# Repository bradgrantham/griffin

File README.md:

# m68k-leftovers

An M68000 homebrew SBC.  See the [design notes](griffin.yml).

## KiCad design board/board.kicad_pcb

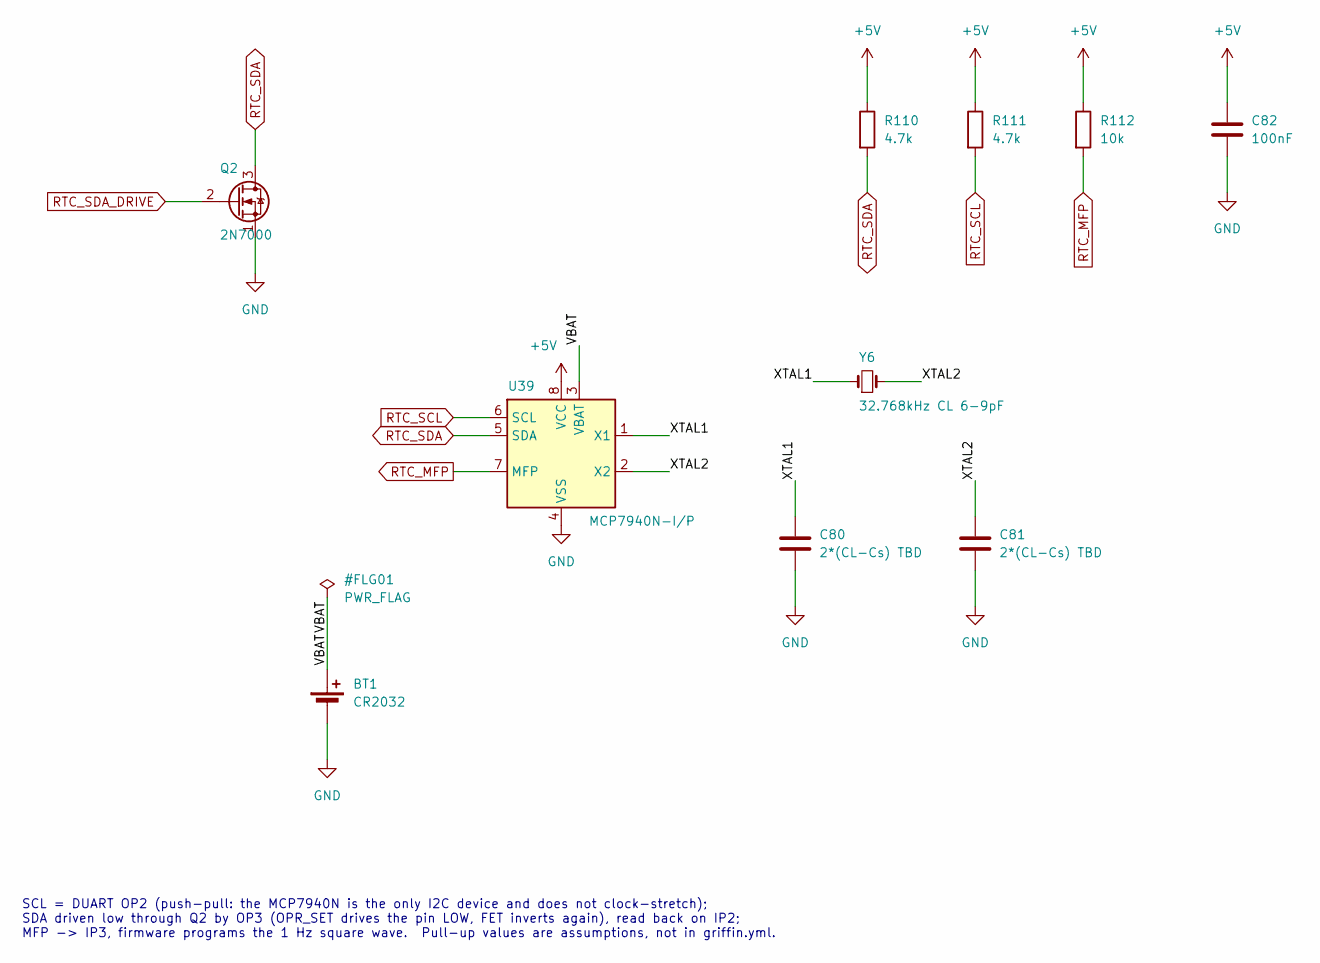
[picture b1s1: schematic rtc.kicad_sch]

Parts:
BT1: CR2032; BatteryHolder_Keystone_3034_1x20mm
C80, C81: 2*(CL-Cs) TBD; C_Disc_D5.0mm_W2.5mm_P5.00mm
C82: 100nF; C_Disc_D5.0mm_W2.5mm_P5.00mm
Q2: 2N7000; TO-92_Inline
R110, R111: 4.7k; R_Axial_DIN0207_L6.3mm_D2.5mm_P10.16mm_Horizontal
R112: 10k; R_Axial_DIN0207_L6.3mm_D2.5mm_P10.16mm_Horizontal
U39: MCP7940N-I/P; DIP-8_W7.62mm
Y6: 32.768kHz CL 6-9pF; Crystal_C26-LF_D2.1mm_L6.5mm_Vertical

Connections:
+5V: C82.1, R110.1, R111.1, R112.1, U39.8 (VCC); also elsewhere on the board
/RTC/XTAL1: C80.1, U39.1 (X1), Y6.1
/RTC/XTAL2: C81.1, U39.2 (X2), Y6.2
GND: BT1.2 (-), C80.2, C81.2, C82.2, Q2.1 (S), U39.4 (VSS); also elsewhere on the board
RTC_MFP: R112.2, U39.7 (MFP)
RTC_SCL: R111.2, U39.6 (SCL)
RTC_SDA: Q2.3 (D), R110.2, U39.5 (SDA)
RTC_SDA_DRIVE: Q2.2 (G)

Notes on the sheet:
SCL = DUART OP2 (push-pull: the MCP7940N is the only I2C device and does not clock-stretch); SDA driven low through Q2 by OP3 (OPR_SET drives the pin LOW, FET inverts again), read back on IP2; MFP -> IP3, firmware programs the 1 Hz square wave. Pull-up values are assumptions, not in griffin.yml.

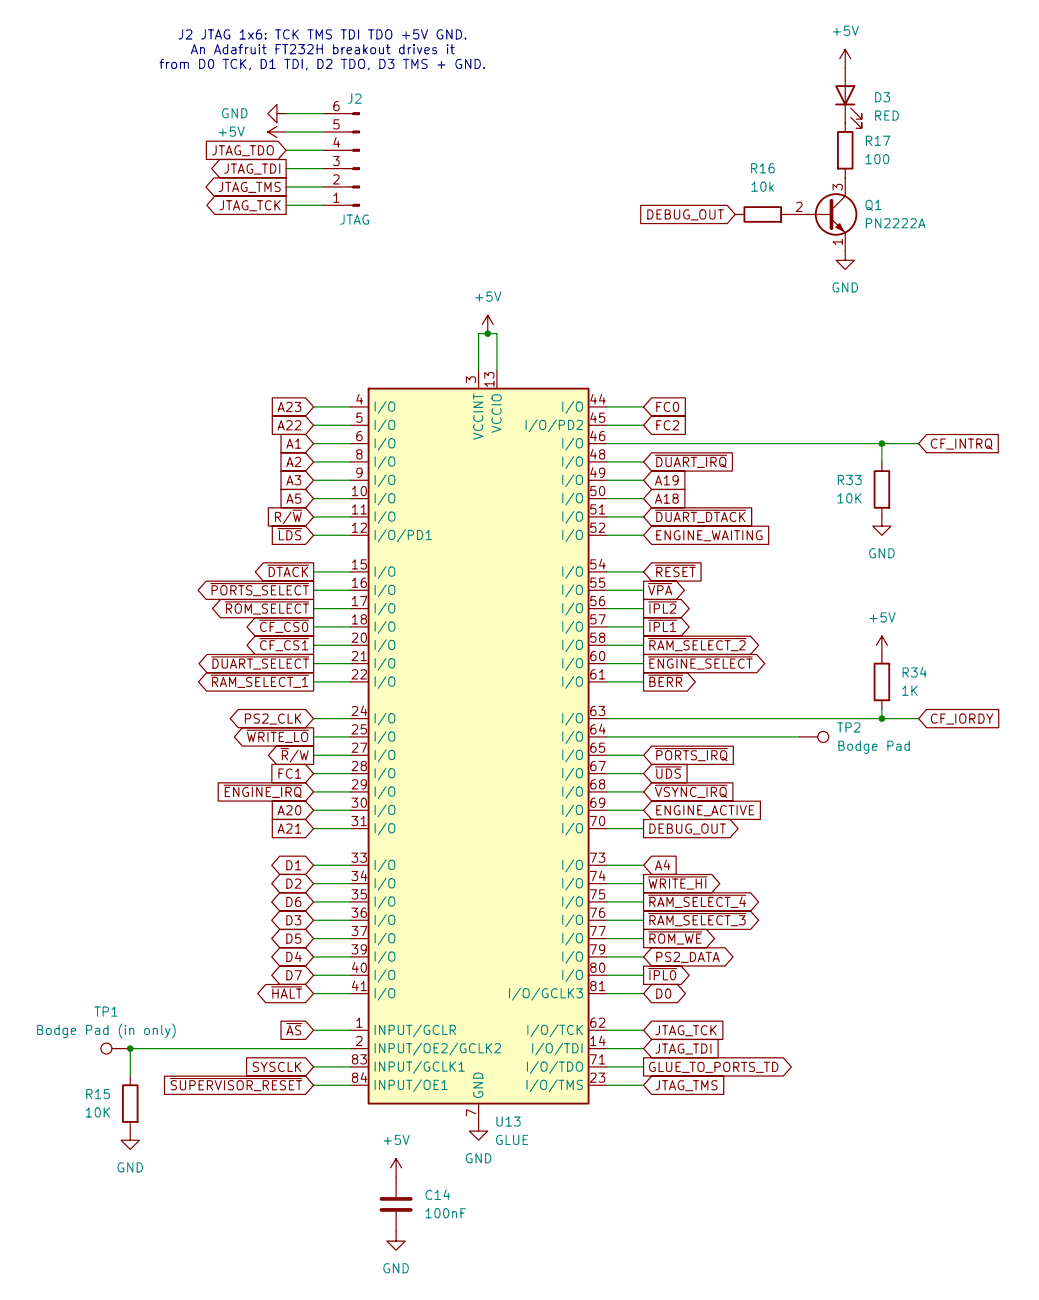
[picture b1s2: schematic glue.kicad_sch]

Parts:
C14: 100nF; C_Disc_D5.0mm_W2.5mm_P5.00mm
D3: RED; LED_D3.0mm
J2: JTAG; PinHeader_1x06_P2.54mm_Vertical
Q1: PN2222A; TO-92_Inline
R15, R33: 10K; R_Axial_DIN0207_L6.3mm_D2.5mm_P10.16mm_Horizontal
R16: 10k; R_Axial_DIN0207_L6.3mm_D2.5mm_P10.16mm_Horizontal
R17: 100; R_Axial_DIN0207_L6.3mm_D2.5mm_P10.16mm_Horizontal
R34: 1K; R_Axial_DIN0207_L6.3mm_D2.5mm_P10.16mm_Horizontal
TP1: Bodge Pad (in only)
TP2: Bodge Pad
U13: GLUE; PLCC-84_THT-Socket

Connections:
+5V: C14.1, D3.2 (A), J2.5, R34.1, U13.3 (VCCINT), U13.13 (VCCIO), U13.26 (VCCIO), U13.38 (VCCIO), U13.43 (VCCINT), U13.53 (VCCIO), U13.66 (VCCIO), U13.78 (VCCIO); also elsewhere on the board
A1: U13.6 (I/O); also elsewhere on the board
A2: U13.8 (I/O); also elsewhere on the board
A3: U13.9 (I/O); also elsewhere on the board
A4: U13.73 (I/O); also elsewhere on the board
A5: U13.10 (I/O); also elsewhere on the board
A18: U13.50 (I/O); also elsewhere on the board
A19: U13.49 (I/O); also elsewhere on the board
A20: U13.30 (I/O); also elsewhere on the board
A21: U13.31 (I/O); also elsewhere on the board
A22: U13.5 (I/O); also elsewhere on the board
A23: U13.4 (I/O); also elsewhere on the board
CF_INTRQ: R33.1, U13.46 (I/O); also elsewhere on the board
CF_IORDY: R34.2, U13.63 (I/O); also elsewhere on the board
D0: U13.81 (I/O/GCLK3); also elsewhere on the board
D1: U13.33 (I/O); also elsewhere on the board
D2: U13.34 (I/O); also elsewhere on the board
D3: U13.36 (I/O); also elsewhere on the board
D4: U13.39 (I/O); also elsewhere on the board
D5: U13.37 (I/O); also elsewhere on the board
D6: U13.35 (I/O); also elsewhere on the board
D7: U13.40 (I/O); also elsewhere on the board
DEBUG_OUT: R16.1, U13.70 (I/O)
ENGINE_ACTIVE: U13.69 (I/O); also elsewhere on the board
ENGINE_WAITING: U13.52 (I/O); also elsewhere on the board
FC0: U13.44 (I/O); also elsewhere on the board
FC1: U13.28 (I/O); also elsewhere on the board
FC2: U13.45 (I/O/PD2); also elsewhere on the board
GLUE_TO_PORTS_TD: U13.71 (I/O/TDO); also elsewhere on the board
GND: C14.2, J2.6, Q1.1 (E), R15.2, R33.2, U13.7 (GND), U13.19 (GND), U13.32 (GND), U13.42 (GND), U13.47 (GND), U13.59 (GND), U13.72 (GND), U13.82 (GND); also elsewhere on the board
JTAG_TCK: J2.1, U13.62 (I/O/TCK); also elsewhere on the board
JTAG_TDI: J2.3, U13.14 (I/O/TDI)
JTAG_TDO: J2.4; also elsewhere on the board
JTAG_TMS: J2.2, U13.23 (I/O/TMS); also elsewhere on the board
unnamed: D3.1 (K), R17.1
unnamed: Q1.2 (B), R16.2
unnamed: Q1.3 (C), R17.2
unnamed: TP2.1, U13.64 (I/O)
unnamed: R15.1, TP1.1, U13.2 (INPUT/OE2/GCLK2)
PS2_CLK: U13.24 (I/O); also elsewhere on the board
PS2_DATA: U13.79 (I/O); also elsewhere on the board
R/~W: U13.11 (I/O); also elsewhere on the board
SYSCLK: U13.83 (INPUT/GCLK1); also elsewhere on the board
~AS: U13.1 (INPUT/GCLR); also elsewhere on the board
~BERR: U13.61 (I/O); also elsewhere on the board
~CF_CS0: U13.18 (I/O); also elsewhere on the board
~CF_CS1: U13.20 (I/O); also elsewhere on the board
~DTACK: U13.15 (I/O); also elsewhere on the board
~DUART_DTACK: U13.51 (I/O)
~DUART_IRQ: U13.48 (I/O)
~DUART_SELECT: U13.21 (I/O)
~ENGINE_IRQ: U13.29 (I/O); also elsewhere on the board
~ENGINE_SELECT: U13.60 (I/O); also elsewhere on the board
~HALT: U13.41 (I/O); also elsewhere on the board
~IPL0: U13.80 (I/O); also elsewhere on the board
~IPL1: U13.57 (I/O); also elsewhere on the board
~IPL2: U13.56 (I/O); also elsewhere on the board
~LDS: U13.12 (I/O/PD1); also elsewhere on the board
~PORTS_IRQ: U13.65 (I/O); also elsewhere on the board
~PORTS_SELECT: U13.16 (I/O); also elsewhere on the board
~RAM_SELECT_1: U13.22 (I/O); also elsewhere on the board
~RAM_SELECT_2: U13.58 (I/O); also elsewhere on the board
~RAM_SELECT_3: U13.76 (I/O); also elsewhere on the board
~RAM_SELECT_4: U13.75 (I/O); also elsewhere on the board
~RESET: U13.54 (I/O); also elsewhere on the board
~ROM_SELECT: U13.17 (I/O); also elsewhere on the board
~ROM_WE: U13.77 (I/O); also elsewhere on the board
~R/W: U13.27 (I/O); also elsewhere on the board
~SUPERVISOR_RESET: U13.84 (INPUT/OE1); also elsewhere on the board
~UDS: U13.67 (I/O); also elsewhere on the board
~VPA: U13.55 (I/O); also elsewhere on the board
~VSYNC_IRQ: U13.68 (I/O); also elsewhere on the board
~WRITE_HI: U13.74 (I/O); also elsewhere on the board
~WRITE_LO: U13.25 (I/O); also elsewhere on the board

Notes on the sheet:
J2 JTAG 1x6: TCK TMS TDI TDO +5V GND. An Adafruit FT232H breakout drives it from D0 TCK, D1 TDI, D2 TDO, D3 TMS + GND.

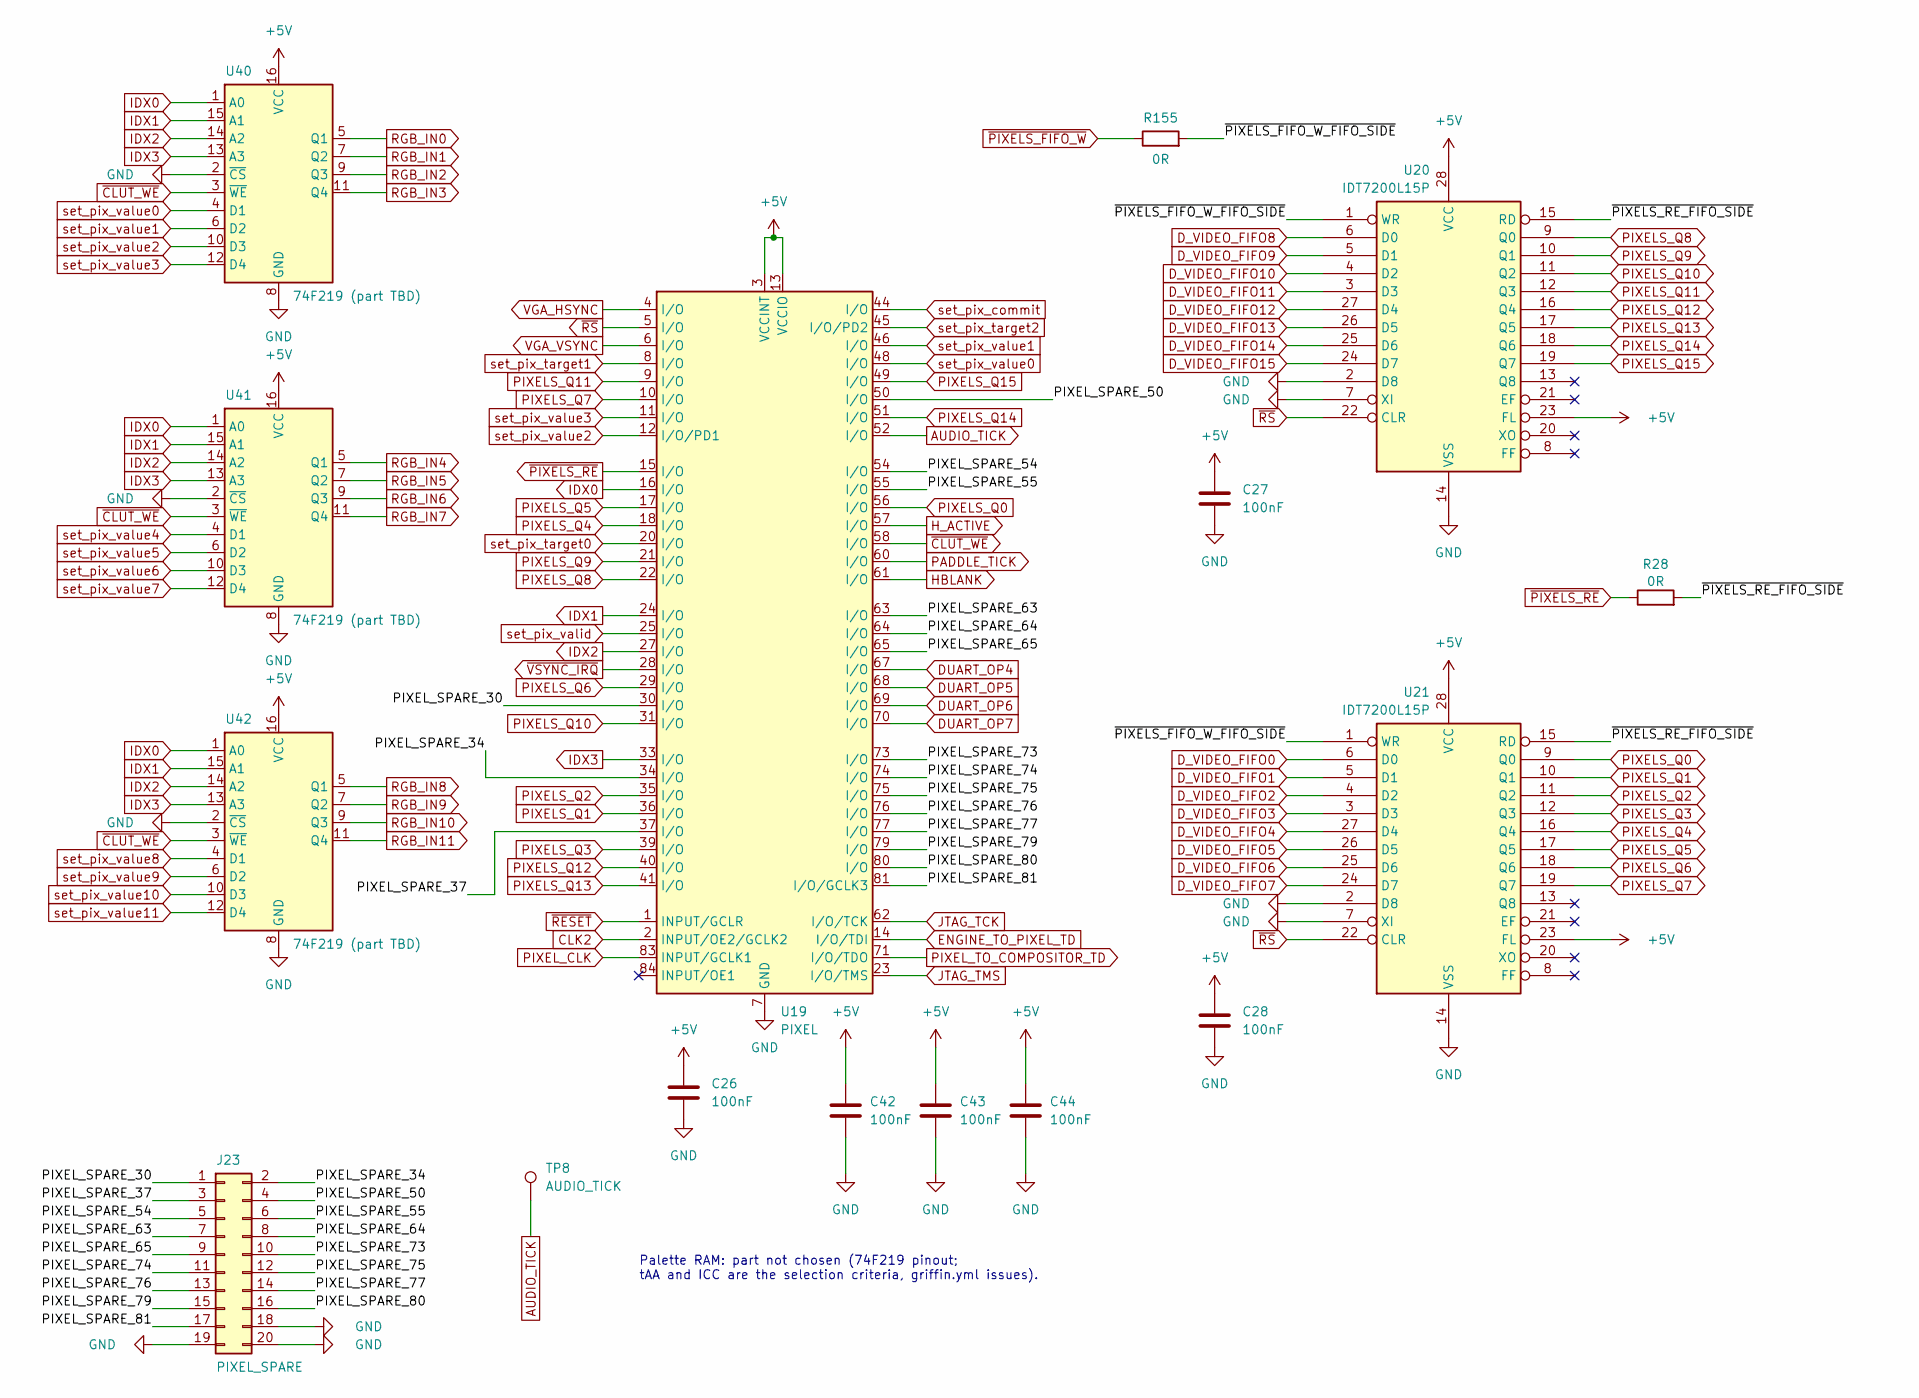
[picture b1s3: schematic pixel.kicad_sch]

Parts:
C26, C27, C28, C42, C43, C44: 100nF; C_Disc_D5.0mm_W2.5mm_P5.00mm
J23: PIXEL_SPARE; PinHeader_2x10_P2.54mm_Vertical
R28, R155: 0R; R_Axial_DIN0207_L6.3mm_D2.5mm_P10.16mm_Horizontal
TP8: AUDIO_TICK; TestPoint_Pad_D1.5mm
U19: PIXEL; PLCC-84_THT-Socket
U20, U21: IDT7200L15P; DIP-28_W7.62mm
U40, U41, U42: 74F219 (part TBD); DIP-16_W7.62mm

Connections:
+5V: C26.1, C27.1, C28.1, C42.1, C43.1, C44.1, U19.3 (VCCINT), U19.13 (VCCIO), U19.26 (VCCIO), U19.38 (VCCIO), U19.43 (VCCINT), U19.53 (VCCIO), U19.66 (VCCIO), U19.78 (VCCIO), U20.23 (FL), U20.28 (VCC), U21.23 (FL), U21.28 (VCC), U40.16 (VCC), U41.16 (VCC), U42.16 (VCC); also elsewhere on the board
/PIXEL/PIXEL_SPARE_30: J23.1, U19.30 (I/O)
/PIXEL/PIXEL_SPARE_34: J23.2, U19.34 (I/O)
/PIXEL/PIXEL_SPARE_37: J23.3, U19.37 (I/O)
/PIXEL/PIXEL_SPARE_50: J23.4, U19.50 (I/O)
/PIXEL/PIXEL_SPARE_54: J23.5, U19.54 (I/O)
/PIXEL/PIXEL_SPARE_55: J23.6, U19.55 (I/O)
/PIXEL/PIXEL_SPARE_63: J23.7, U19.63 (I/O)
/PIXEL/PIXEL_SPARE_64: J23.8, U19.64 (I/O)
/PIXEL/PIXEL_SPARE_65: J23.9, U19.65 (I/O)
/PIXEL/PIXEL_SPARE_73: J23.10, U19.73 (I/O)
/PIXEL/PIXEL_SPARE_74: J23.11, U19.74 (I/O)
/PIXEL/PIXEL_SPARE_75: J23.12, U19.75 (I/O)
/PIXEL/PIXEL_SPARE_76: J23.13, U19.76 (I/O)
/PIXEL/PIXEL_SPARE_77: J23.14, U19.77 (I/O)
/PIXEL/PIXEL_SPARE_79: J23.15, U19.79 (I/O)
/PIXEL/PIXEL_SPARE_80: J23.16, U19.80 (I/O)
/PIXEL/PIXEL_SPARE_81: J23.17, U19.81 (I/O/GCLK3)
/PIXEL/~PIXELS_FIFO_W_FIFO_SIDE: R155.2, U20.1 (WR), U21.1 (WR)
/PIXEL/~PIXELS_RE_FIFO_SIDE: R28.2, U20.15 (RD), U21.15 (RD)
AUDIO_TICK: TP8.1, U19.52 (I/O)
CLK2: U19.2 (INPUT/OE2/GCLK2); also elsewhere on the board
DUART_OP4: U19.67 (I/O)
DUART_OP5: U19.68 (I/O)
DUART_OP6: U19.69 (I/O)
DUART_OP7: U19.70 (I/O)
D_VIDEO_FIFO0: U21.6 (D0); also elsewhere on the board
D_VIDEO_FIFO1: U21.5 (D1); also elsewhere on the board
D_VIDEO_FIFO2: U21.4 (D2); also elsewhere on the board
D_VIDEO_FIFO3: U21.3 (D3); also elsewhere on the board
D_VIDEO_FIFO4: U21.27 (D4); also elsewhere on the board
D_VIDEO_FIFO5: U21.26 (D5); also elsewhere on the board
D_VIDEO_FIFO6: U21.25 (D6); also elsewhere on the board
D_VIDEO_FIFO7: U21.24 (D7); also elsewhere on the board
D_VIDEO_FIFO8: U20.6 (D0); also elsewhere on the board
D_VIDEO_FIFO9: U20.5 (D1); also elsewhere on the board
D_VIDEO_FIFO10: U20.4 (D2); also elsewhere on the board
D_VIDEO_FIFO11: U20.3 (D3); also elsewhere on the board
D_VIDEO_FIFO12: U20.27 (D4); also elsewhere on the board
D_VIDEO_FIFO13: U20.26 (D5); also elsewhere on the board
D_VIDEO_FIFO14: U20.25 (D6); also elsewhere on the board
D_VIDEO_FIFO15: U20.24 (D7); also elsewhere on the board
ENGINE_TO_PIXEL_TD: U19.14 (I/O/TDI); also elsewhere on the board
GND: C26.2, C27.2, C28.2, C42.2, C43.2, C44.2, J23.18, J23.19, J23.20, U19.7 (GND), U19.19 (GND), U19.32 (GND), U19.42 (GND), U19.47 (GND), U19.59 (GND), U19.72 (GND), U19.82 (GND), U20.2 (D8), U20.7 (XI), U20.14 (VSS), U21.2 (D8), U21.7 (XI), U21.14 (VSS), U40.2 (~CS), U40.8 (GND), U41.2 (~CS), U41.8 (GND), U42.2 (~CS), U42.8 (GND); also elsewhere on the board
HBLANK: U19.61 (I/O); also elsewhere on the board
H_ACTIVE: U19.57 (I/O); also elsewhere on the board
IDX0: U19.16 (I/O), U40.1 (A0), U41.1 (A0), U42.1 (A0)
IDX1: U19.24 (I/O), U40.15 (A1), U41.15 (A1), U42.15 (A1)
IDX2: U19.27 (I/O), U40.14 (A2), U41.14 (A2), U42.14 (A2)
IDX3: U19.33 (I/O), U40.13 (A3), U41.13 (A3), U42.13 (A3)
JTAG_TCK: U19.62 (I/O/TCK); also elsewhere on the board
JTAG_TMS: U19.23 (I/O/TMS); also elsewhere on the board
PADDLE_TICK: U19.60 (I/O); also elsewhere on the board
PIXELS_Q0: U19.56 (I/O), U21.9 (Q0)
PIXELS_Q1: U19.36 (I/O), U21.10 (Q1)
PIXELS_Q2: U19.35 (I/O), U21.11 (Q2)
PIXELS_Q3: U19.39 (I/O), U21.12 (Q3)
PIXELS_Q4: U19.18 (I/O), U21.16 (Q4)
PIXELS_Q5: U19.17 (I/O), U21.17 (Q5)
PIXELS_Q6: U19.29 (I/O), U21.18 (Q6)
PIXELS_Q7: U19.10 (I/O), U21.19 (Q7)
PIXELS_Q8: U19.22 (I/O), U20.9 (Q0)
PIXELS_Q9: U19.21 (I/O), U20.10 (Q1)
PIXELS_Q10: U19.31 (I/O), U20.11 (Q2)
PIXELS_Q11: U19.9 (I/O), U20.12 (Q3)
PIXELS_Q12: U19.40 (I/O), U20.16 (Q4)
PIXELS_Q13: U19.41 (I/O), U20.17 (Q5)
PIXELS_Q14: U19.51 (I/O), U20.18 (Q6)
PIXELS_Q15: U19.49 (I/O), U20.19 (Q7)
PIXEL_CLK: U19.83 (INPUT/GCLK1); also elsewhere on the board
PIXEL_TO_COMPOSITOR_TD: U19.71 (I/O/TDO); also elsewhere on the board
RGB_IN0: U40.5 (Q1); also elsewhere on the board
RGB_IN1: U40.7 (Q2); also elsewhere on the board
RGB_IN2: U40.9 (Q3); also elsewhere on the board
RGB_IN3: U40.11 (Q4); also elsewhere on the board
RGB_IN4: U41.5 (Q1); also elsewhere on the board
RGB_IN5: U41.7 (Q2); also elsewhere on the board
RGB_IN6: U41.9 (Q3); also elsewhere on the board
RGB_IN7: U41.11 (Q4); also elsewhere on the board
RGB_IN8: U42.5 (Q1); also elsewhere on the board
RGB_IN9: U42.7 (Q2); also elsewhere on the board
RGB_IN10: U42.9 (Q3); also elsewhere on the board
RGB_IN11: U42.11 (Q4); also elsewhere on the board
VGA_HSYNC: U19.4 (I/O); also elsewhere on the board
VGA_VSYNC: U19.6 (I/O); also elsewhere on the board
set_pix_commit: U19.44 (I/O); also elsewhere on the board
set_pix_target0: U19.20 (I/O); also elsewhere on the board
set_pix_target1: U19.8 (I/O); also elsewhere on the board
set_pix_target2: U19.45 (I/O/PD2); also elsewhere on the board
set_pix_valid: U19.25 (I/O); also elsewhere on the board
set_pix_value0: U19.48 (I/O), U40.4 (D1); also elsewhere on the board
set_pix_value1: U19.46 (I/O), U40.6 (D2); also elsewhere on the board
set_pix_value2: U19.12 (I/O/PD1), U40.10 (D3); also elsewhere on the board
set_pix_value3: U19.11 (I/O), U40.12 (D4); also elsewhere on the board
set_pix_value4: U41.4 (D1); also elsewhere on the board
set_pix_value5: U41.6 (D2); also elsewhere on the board
set_pix_value6: U41.10 (D3); also elsewhere on the board
set_pix_value7: U41.12 (D4); also elsewhere on the board
set_pix_value8: U42.4 (D1); also elsewhere on the board
set_pix_value9: U42.6 (D2); also elsewhere on the board
set_pix_value10: U42.10 (D3); also elsewhere on the board
set_pix_value11: U42.12 (D4); also elsewhere on the board
~CLUT_WE: U19.58 (I/O), U40.3 (~WE), U41.3 (~WE), U42.3 (~WE)
~PIXELS_FIFO_W: R155.1; also elsewhere on the board
~PIXELS_RE: R28.1, U19.15 (I/O)
~RESET: U19.1 (INPUT/GCLR); also elsewhere on the board
~RS: U19.5 (I/O), U20.22 (CLR), U21.22 (CLR); also elsewhere on the board
~VSYNC_IRQ: U19.28 (I/O); also elsewhere on the board

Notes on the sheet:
Palette RAM: part not chosen (74F219 pinout; tAA and ICC are the selection criteria, griffin.yml issues).

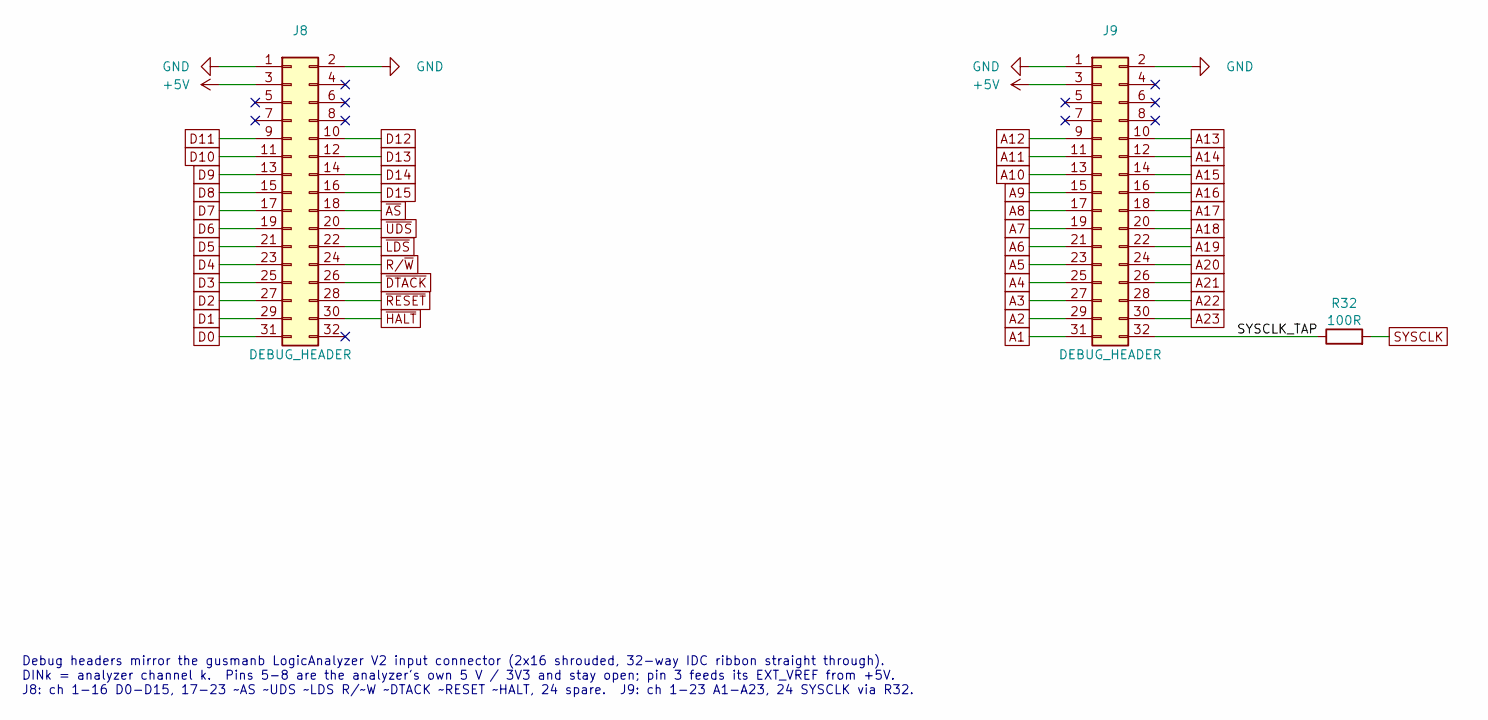
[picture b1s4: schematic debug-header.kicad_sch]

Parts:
J8, J9: DEBUG_HEADER; IDC-Header_2x16_P2.54mm_Vertical
R32: 100R; R_Axial_DIN0207_L6.3mm_D2.5mm_P10.16mm_Horizontal

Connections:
+5V: J8.3, J9.3; also elsewhere on the board
/DEBUG_HEADER/SYSCLK_TAP: J9.32, R32.1
A1: J9.31; also elsewhere on the board
A2: J9.29; also elsewhere on the board
A3: J9.27; also elsewhere on the board
A4: J9.25; also elsewhere on the board
A5: J9.23; also elsewhere on the board
A6: J9.21; also elsewhere on the board
A7: J9.19; also elsewhere on the board
A8: J9.17; also elsewhere on the board
A9: J9.15; also elsewhere on the board
A10: J9.13; also elsewhere on the board
A11: J9.11; also elsewhere on the board
A12: J9.9; also elsewhere on the board
A13: J9.10; also elsewhere on the board
A14: J9.12; also elsewhere on the board
A15: J9.14; also elsewhere on the board
A16: J9.16; also elsewhere on the board
A17: J9.18; also elsewhere on the board
A18: J9.20; also elsewhere on the board
A19: J9.22; also elsewhere on the board
A20: J9.24; also elsewhere on the board
A21: J9.26; also elsewhere on the board
A22: J9.28; also elsewhere on the board
A23: J9.30; also elsewhere on the board
D0: J8.31; also elsewhere on the board
D1: J8.29; also elsewhere on the board
D2: J8.27; also elsewhere on the board
D3: J8.25; also elsewhere on the board
D4: J8.23; also elsewhere on the board
D5: J8.21; also elsewhere on the board
D6: J8.19; also elsewhere on the board
D7: J8.17; also elsewhere on the board
D8: J8.15; also elsewhere on the board
D9: J8.13; also elsewhere on the board
D10: J8.11; also elsewhere on the board
D11: J8.9; also elsewhere on the board
D12: J8.10; also elsewhere on the board
D13: J8.12; also elsewhere on the board
D14: J8.14; also elsewhere on the board
D15: J8.16; also elsewhere on the board
GND: J8.1, J8.2, J9.1, J9.2; also elsewhere on the board
R/~W: J8.24; also elsewhere on the board
SYSCLK: R32.2; also elsewhere on the board
~AS: J8.18; also elsewhere on the board
~DTACK: J8.26; also elsewhere on the board
~HALT: J8.30; also elsewhere on the board
~LDS: J8.22; also elsewhere on the board
~RESET: J8.28; also elsewhere on the board
~UDS: J8.20; also elsewhere on the board

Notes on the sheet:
Debug headers mirror the gusmanb LogicAnalyzer V2 input connector (2x16 shrouded, 32-way IDC ribbon straight through). DINk = analyzer channel k. Pins 5-8 are the analyzer's own 5 V / 3V3 and stay open; pin 3 feeds its EXT_VREF from +5V. J8: ch 1-16 D0-D15, 17-23 ~AS ~UDS ~LDS R/~W ~DTACK ~RESET ~H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

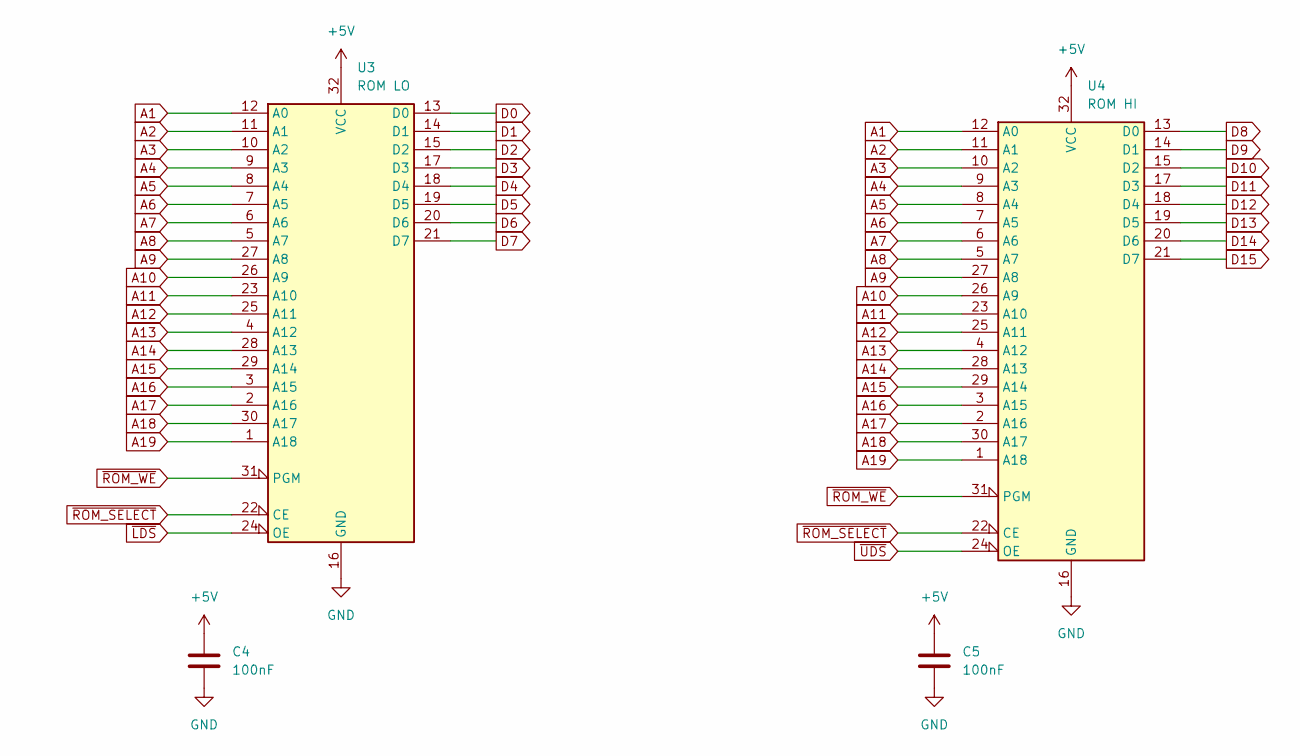
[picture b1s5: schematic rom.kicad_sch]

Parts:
C4, C5: 100nF; C_Disc_D5.0mm_W2.5mm_P5.00mm
U3: ROM LO; DIP-32_W15.24mm
U4: ROM HI; DIP-32_W15.24mm

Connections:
+5V: C4.1, C5.1, U3.32 (VCC), U4.32 (VCC); also elsewhere on the board
A1: U3.12 (A0), U4.12 (A0); also elsewhere on the board
A2: U3.11 (A1), U4.11 (A1); also elsewhere on the board
A3: U3.10 (A2), U4.10 (A2); also elsewhere on the board
A4: U3.9 (A3), U4.9 (A3); also elsewhere on the board
A5: U3.8 (A4), U4.8 (A4); also elsewhere on the board
A6: U3.7 (A5), U4.7 (A5); also elsewhere on the board
A7: U3.6 (A6), U4.6 (A6); also elsewhere on the board
A8: U3.5 (A7), U4.5 (A7); also elsewhere on the board
A9: U3.27 (A8), U4.27 (A8); also elsewhere on the board
A10: U3.26 (A9), U4.26 (A9); also elsewhere on the board
A11: U3.23 (A10), U4.23 (A10); also elsewhere on the board
A12: U3.25 (A11), U4.25 (A11); also elsewhere on the board
A13: U3.4 (A12), U4.4 (A12); also elsewhere on the board
A14: U3.28 (A13), U4.28 (A13); also elsewhere on the board
A15: U3.29 (A14), U4.29 (A14); also elsewhere on the board
A16: U3.3 (A15), U4.3 (A15); also elsewhere on the board
A17: U3.2 (A16), U4.2 (A16); also elsewhere on the board
A18: U3.30 (A17), U4.30 (A17); also elsewhere on the board
A19: U3.1 (A18), U4.1 (A18); also elsewhere on the board
D0: U3.13 (D0); also elsewhere on the board
D1: U3.14 (D1); also elsewhere on the board
D2: U3.15 (D2); also elsewhere on the board
D3: U3.17 (D3); also elsewhere on the board
D4: U3.18 (D4); also elsewhere on the board
D5: U3.19 (D5); also elsewhere on the board
D6: U3.20 (D6); also elsewhere on the board
D7: U3.21 (D7); also elsewhere on the board
D8: U4.13 (D0); also elsewhere on the board
D9: U4.14 (D1); also elsewhere on the board
D10: U4.15 (D2); also elsewhere on the board
D11: U4.17 (D3); also elsewhere on the board
D12: U4.18 (D4); also elsewhere on the board
D13: U4.19 (D5); also elsewhere on the board
D14: U4.20 (D6); also elsewhere on the board
D15: U4.21 (D7); also elsewhere on the board
GND: C4.2, C5.2, U3.16 (GND), U4.16 (GND); also elsewhere on the board
~LDS: U3.24 (OE); also elsewhere on the board
~ROM_SELECT: U3.22 (CE), U4.22 (CE); also elsewhere on the board
~ROM_WE: U3.31 (PGM), U4.31 (PGM); also elsewhere on the board
~UDS: U4.24 (OE); also elsewhere on the board

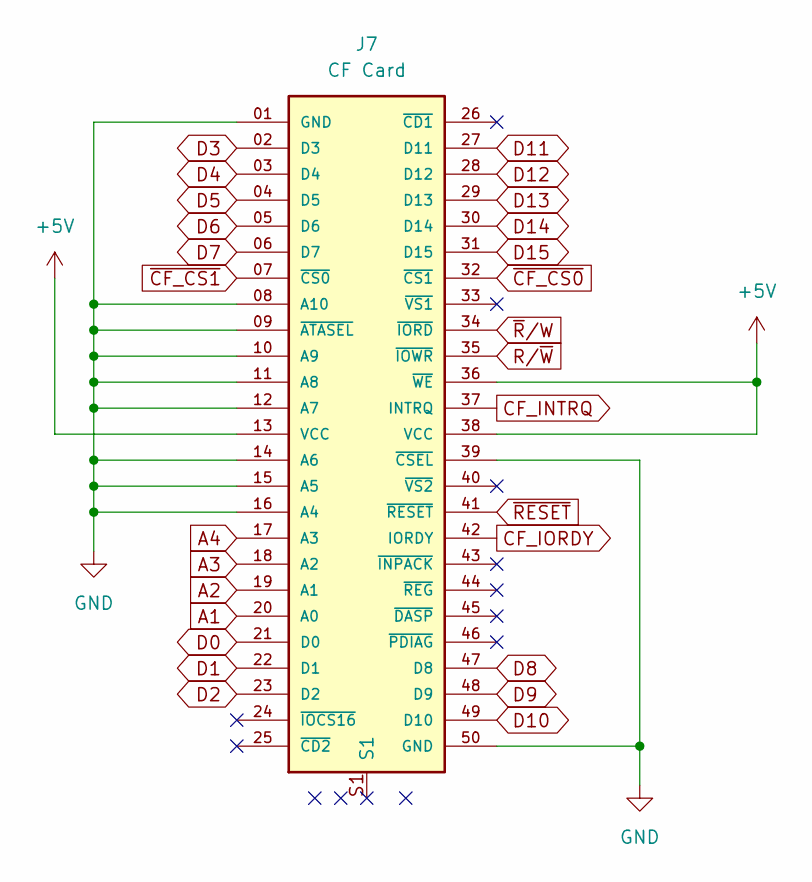
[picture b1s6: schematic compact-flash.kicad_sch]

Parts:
J7: CF Card; SAMTEC_CFT-125-01-L-D-RA-01-SL; PARTREV A

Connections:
+5V: J7.13 (VCC), J7.36 (~WE), J7.38 (VCC); also elsewhere on the board
A1: J7.20 (A0); also elsewhere on the board
A2: J7.19 (A1); also elsewhere on the board
A3: J7.18 (A2); also elsewhere on the board
A4: J7.17 (A3); also elsewhere on the board
CF_INTRQ: J7.37 (INTRQ); also elsewhere on the board
CF_IORDY: J7.42 (IORDY); also elsewhere on the board
D0: J7.21 (D0); also elsewhere on the board
D1: J7.22 (D1); also elsewhere on the board
D2: J7.23 (D2); also elsewhere on the board
D3: J7.02 (D3); also elsewhere on the board
D4: J7.03 (D4); also elsewhere on the board
D5: J7.04 (D5); also elsewhere on the board
D6: J7.05 (D6); also elsewhere on the board
D7: J7.06 (D7); also elsewhere on the board
D8: J7.47 (D8); also elsewhere on the board
D9: J7.48 (D9); also elsewhere on the board
D10: J7.49 (D10); also elsewhere on the board
D11: J7.27 (D11); also elsewhere on the board
D12: J7.28 (D12); also elsewhere on the board
D13: J7.29 (D13); also elsewhere on the board
D14: J7.30 (D14); also elsewhere on the board
D15: J7.31 (D15); also elsewhere on the board
GND: J7.01 (GND), J7.08 (A10), J7.09 (~ATASEL), J7.10 (A9), J7.11 (A8), J7.12 (A7), J7.14 (A6), J7.15 (A5), J7.16 (A4), J7.39 (~CSEL), J7.50 (GND); also elsewhere on the board
R/~W: J7.35 (~IOWR); also elsewhere on the board
S2: J7.S2
S3: J7.S3
S4: J7.S4
~CF_CS0: J7.32 (~CS1); also elsewhere on the board
~CF_CS1: J7.07 (~CS0); also elsewhere on the board
~RESET: J7.41 (~RESET); also elsewhere on the board
~R/W: J7.34 (~IORD); also elsewhere on the board

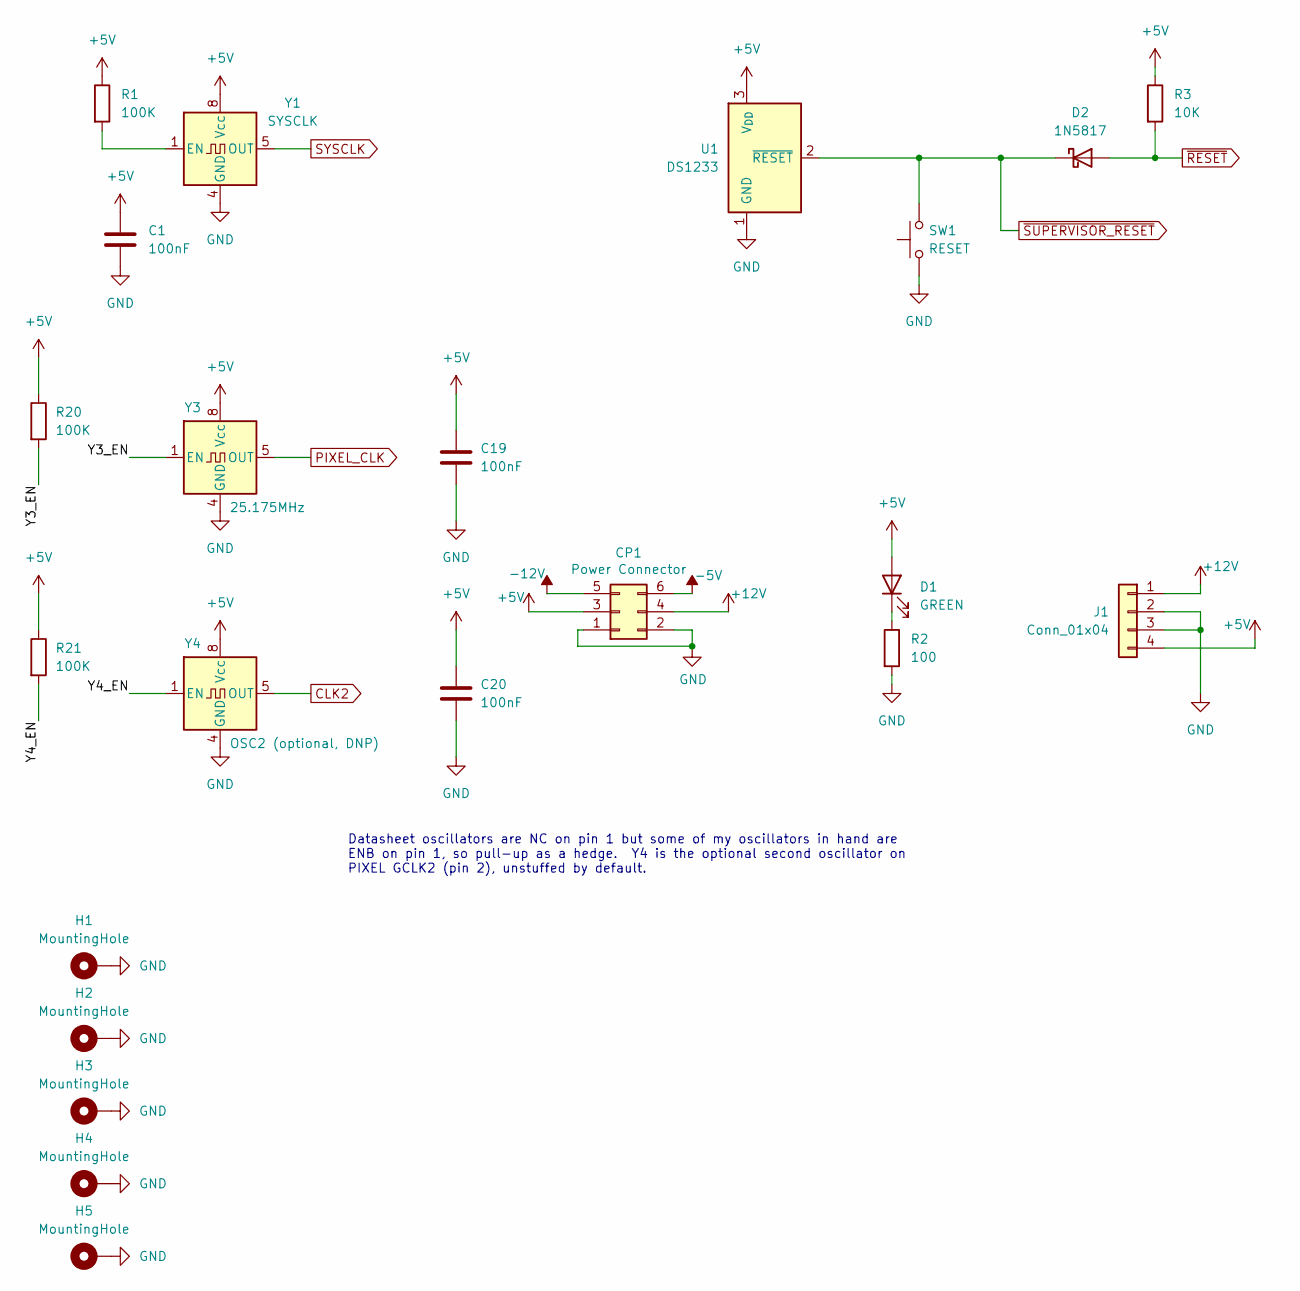
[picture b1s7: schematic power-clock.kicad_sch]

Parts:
C1, C19, C20: 100nF; C_Disc_D5.0mm_W2.5mm_P5.00mm
CP1: Power Connector; POWER; DigiKey A14226-ND
D1: GREEN; LED_D3.0mm
D2: 1N5817; D_DO-41_SOD81_P10.16mm_Horizontal
H1, H2, H3, H4, H5: MountingHole; MountingHole_2.5mm_Pad_Via
J1: Conn_01x04
R1, R20, R21: 100K; R_Axial_DIN0207_L6.3mm_D2.5mm_P10.16mm_Horizontal
R2: 100; R_Axial_DIN0207_L6.3mm_D2.5mm_P10.16mm_Horizontal
R3: 10K; R_Axial_DIN0207_L6.3mm_D2.5mm_P10.16mm_Horizontal
SW1: RESET; SW_TH_Tactile_Omron_B3F-106x
U1: DS1233
Y1: SYSCLK; Oscillator_DIP-8
Y3: 25.175MHz; Oscillator_DIP-8
Y4: OSC2 (optional, DNP); Oscillator_DIP-8

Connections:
+5V: C1.1, C19.1, C20.1, CP1.3, D1.2 (A), J1.4, R1.1, R3.1, R20.1, R21.1, U1.3 (V_{DD}), Y1.8 (Vcc), Y3.8 (Vcc), Y4.8 (Vcc); also elsewhere on the board
/POWER_CLOCK_RESET/Y3_EN: R20.2, Y3.1 (EN)
/POWER_CLOCK_RESET/Y4_EN: R21.2, Y4.1 (EN)
CLK2: Y4.5 (OUT); also elsewhere on the board
GND: C1.2, C19.2, C20.2, CP1.1, CP1.2, H1.1, H2.1, H3.1, H4.1, H5.1, J1.2, J1.3, R2.2, SW1.1, U1.1 (GND), Y1.4 (GND), Y3.4 (GND), Y4.4 (GND); also elsewhere on the board
unnamed: CP1.4, J1.1
unnamed: D1.1 (K), R2.1
unnamed: R1.2, Y1.1 (EN)
PIXEL_CLK: Y3.5 (OUT); also elsewhere on the board
SYSCLK: Y1.5 (OUT); also elsewhere on the board
~RESET: D2.2 (A), R3.2; also elsewhere on the board
~SUPERVISOR_RESET: D2.1 (K), SW1.2, U1.2 (~RESET); also elsewhere on the board

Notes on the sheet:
Datasheet oscillators are NC on pin 1 but some of my oscillators in hand are ENB on pin 1, so pull-up as a hedge. Y4 is the optional second oscillator on PIXEL GCLK2 (pin 2), unstuffed by default.
